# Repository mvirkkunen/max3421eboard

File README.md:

max3421eboard
=============

It's my first PCB. Not verified yet.

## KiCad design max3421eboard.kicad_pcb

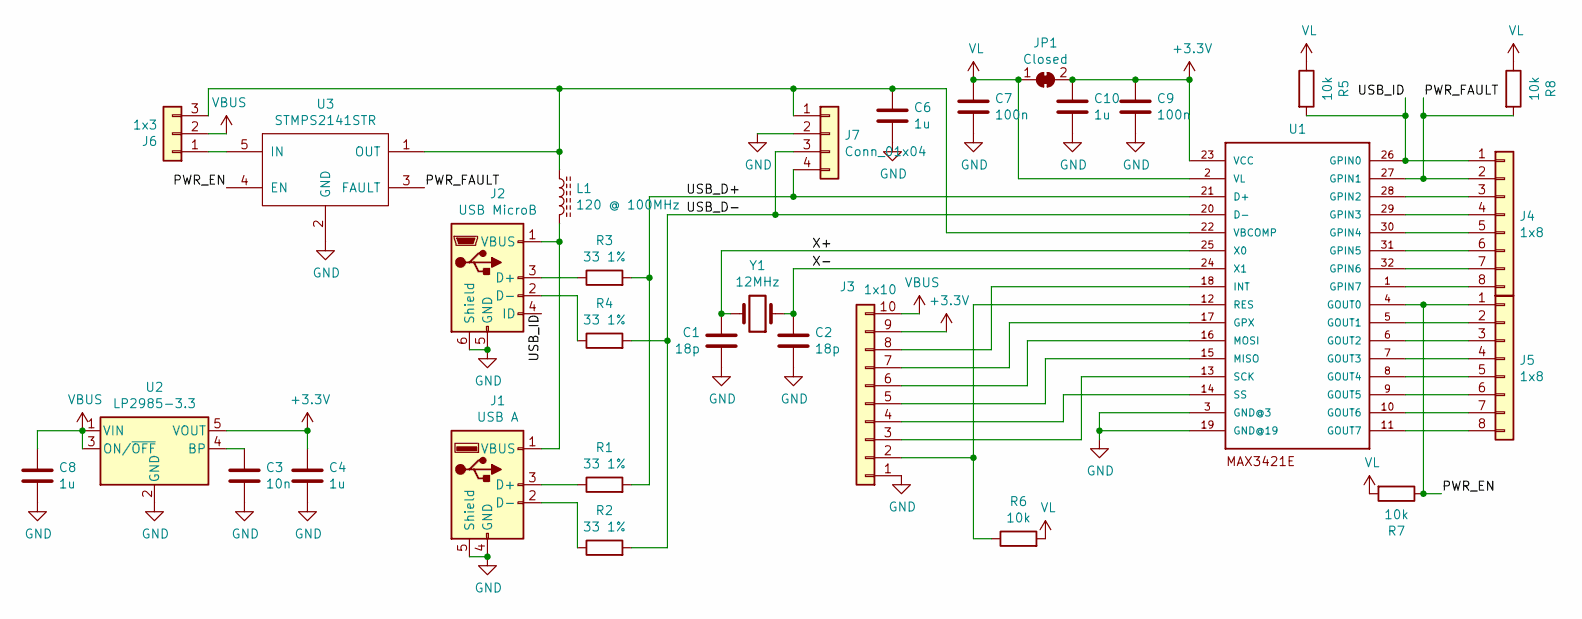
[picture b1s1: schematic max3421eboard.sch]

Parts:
C1, C2: 18p; C_0805_HandSoldering
C3: 10n; C_0805_HandSoldering
C4, C6, C8, C10: 1u; C_0805_HandSoldering
C7, C9: 100n; C_0805_HandSoldering
J1: USB A; USB_A
J2: USB MicroB; USB_Micro-B_10103594-0001LF
J3: 1x10; Pin_Header_Straight_1x10_Pitch2.54mm
J4, J5: 1x8; Pin_Header_Straight_1x08_Pitch2.54mm
J6: 1x3; Pin_Header_Straight_1x03_Pitch2.54mm
J7: Conn_01x04; Pin_Header_Straight_1x04_Pitch2.54mm
JP1: Closed; SolderJumper-2_P1.3mm_Bridged_RoundedPad1.0x1.5mm
L1: 120 @ 100MHz; L_0805_HandSoldering
R1, R2, R3, R4: 33 1%; R_0805_HandSoldering
R5, R6, R7, R8: 10k; R_0805_HandSoldering
U1: MAX3421E; TQFP32-5MM
U2: LP2985-3.3; SOT-23-5_HandSoldering
U3: STMPS2141STR; SOT-23-5
Y1: 12MHz; Crystal_SMD_5032-2pin_5.0x3.2mm_HandSoldering

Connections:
+3V3: C4.1, C9.1, C10.1, J3.9, JP1.2 (B), U1.23 (VCC), U2.5 (VOUT)
/PWR_EN: J5.1, R7.1, U1.4 (GOUT0), U3.4 (EN)
/PWR_FAULT: J4.2, R8.2, U1.27 (GPIN1), U3.3 (FAULT)
/USB_D+: J7.4, R1.2, R3.2, U1.21 (D+)
/USB_D-: J7.3, R2.2, R4.2, U1.20 (D-)
/USB_ID: J2.4 (ID), J4.1, R5.2, U1.26 (GPIN0)
/X+: C1.2, U1.25 (X0), Y1.2
/X-: C2.1, U1.24 (X1), Y1.1
GND: C1.1, C2.2, C3.2, C4.2, C6.2, C7.2, C8.2, C9.2, C10.2, J1.4 (GND), J1.5 (Shield), J2.5 (GND), J2.6 (Shield), J3.1, J7.2, U1.3 (GND@3), U1.19 (GND@19), U2.2 (GND), U3.2 (GND)
unnamed: C3.1, U2.4 (BP)
unnamed: C6.1, J6.3, J7.1, L1.1, U1.22 (VBCOMP), U3.1 (OUT)
unnamed: J1.1 (VBUS), J2.1 (VBUS), L1.2
unnamed: J1.2 (D-), R2.1
unnamed: J1.3 (D+), R1.1
unnamed: J2.2 (D-), R4.1
unnamed: J2.3 (D+), R3.1
unnamed: J3.2, R6.1, U1.12 (RES)
unnamed: J3.3, U1.13 (SCK)
unnamed: J3.4, U1.14 (SS)
unnamed: J3.5, U1.15 (MISO)
unnamed: J3.6, U1.16 (MOSI)
unnamed: J3.7, U1.17 (GPX)
unnamed: J3.8, U1.18 (INT)
unnamed: J4.3, U1.28 (GPIN2)
unnamed: J4.4, U1.29 (GPIN3)
unnamed: J4.5, U1.30 (GPIN4)
unnamed: J4.6, U1.31 (GPIN5)
unnamed: J4.7, U1.32 (GPIN6)
unnamed: J4.8, U1.1 (GPIN7)
unnamed: J5.2, U1.5 (GOUT1)
unnamed: J5.3, U1.6 (GOUT2)
unnamed: J5.4, U1.7 (GOUT3)
unnamed: J5.5, U1.8 (GOUT4)
unnamed: J5.6, U1.9 (GOUT5)
unnamed: J5.7, U1.10 (GOUT6)
unnamed: J5.8, U1.11 (GOUT7)
unnamed: J6.1, U3.5 (IN)
VBUS: C8.1, J3.10, J6.2, U2.1 (VIN), U2.3 (ON/~OFF~)
VL: C7.1, JP1.1 (A), R5.1, R6.2, R7.2, R8.1, U1.2 (VL)

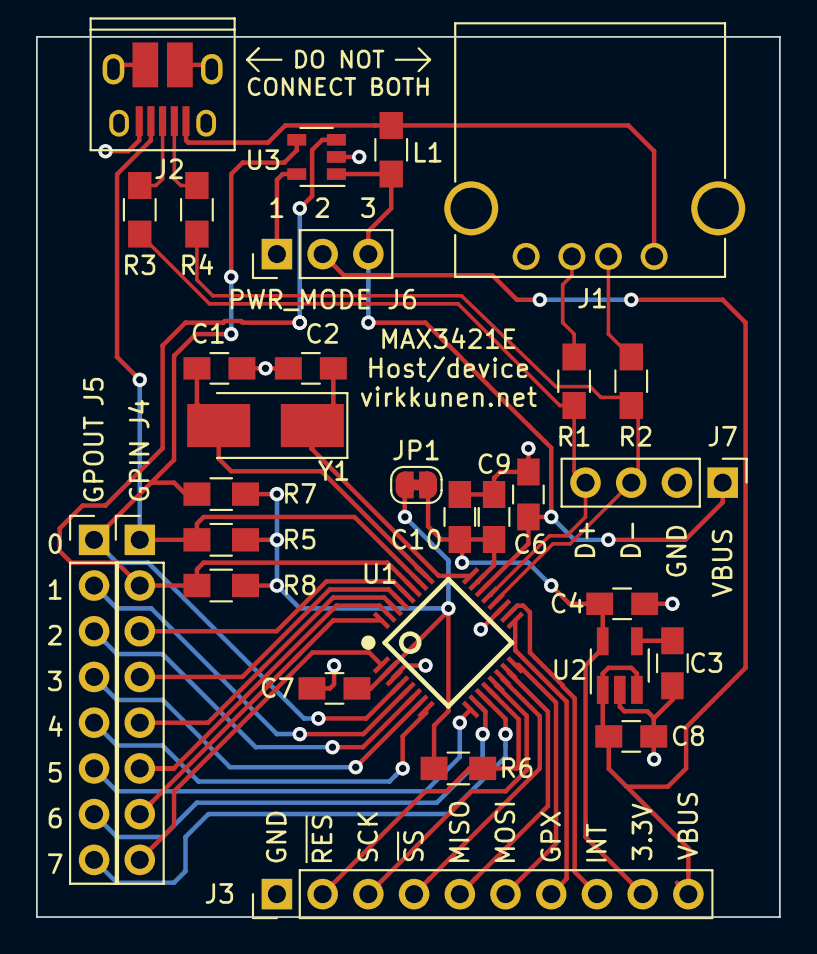
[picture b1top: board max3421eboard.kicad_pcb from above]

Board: 2 copper layers, 41.3 x 48.9 mm, 30 parts (0 on the bottom side), 39 nets.

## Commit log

2020-02-17 Added more filtering/bypass and revised layout
2020-02-17 Moved bypass caps closer to U1
2020-02-17 Add one more cap and move bypass around even more
2020-02-17 Layout clean-up
2020-02-17 Clean-up
2020-02-17 Show layer
2020-02-18 Adjustments
2020-02-18 Move decoupling capacitors around for better filtering
